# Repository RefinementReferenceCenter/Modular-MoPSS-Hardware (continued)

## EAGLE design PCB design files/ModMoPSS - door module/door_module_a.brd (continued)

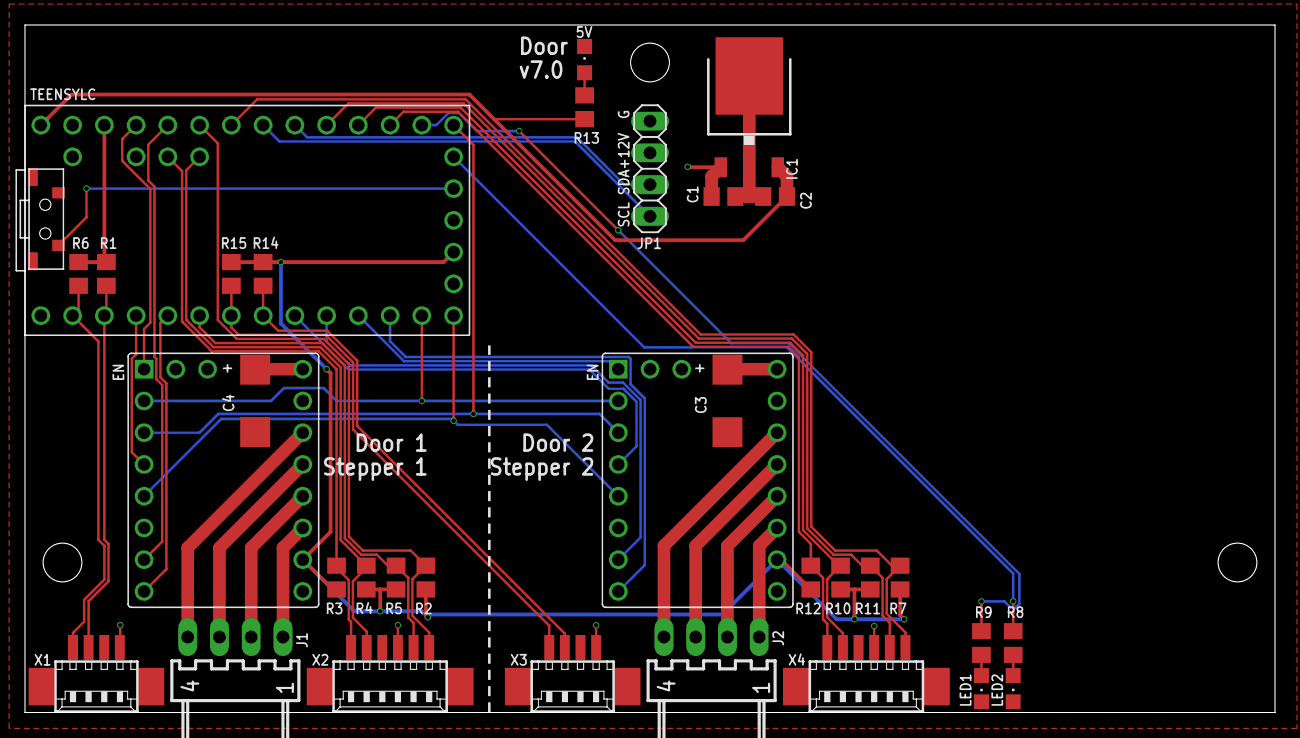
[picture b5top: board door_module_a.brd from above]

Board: 2 copper layers, 100.0 x 55.0 mm, 34 parts (0 on the bottom side), 43 nets.

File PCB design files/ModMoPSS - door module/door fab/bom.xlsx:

Comment | Designator | Footprint | JLCPCB Part #（optional）
red | 5V | CHIPLED_0805 | C84256
u33 | C1 | C0805 | C1740
u1 | C2 | C0805 | C49678
100u16v | C3 | SMC_C | C11375
100u16v | C4 | SMC_C | C11375
7805_TO252 | IC1 | TO252 | C233417
red | LED1 | CHIPLED_0805 | C84256
red | LED2 | CHIPLED_0805 | C84256
47k | R1 | R0805 | C17713
47k | R2 | R0805 | C17713
47k | R3 | R0805 | C17713
47k | R4 | R0805 | C17713
47k | R5 | R0805 | C17713
47k | R6 | R0805 | C17713
47k | R7 | R0805 | C17713
15k | R8 | R0805 | C17475
15k | R9 | R0805 | C17475
47k | R10 | R0805 | C17713
47k | R11 | R0805 | C17713
47k | R12 | R0805 | C17713
20k | R13 | R0805 | C4328
47k | R14 | R0805 | C17713
47k | R15 | R0805 | C17713
KH-3635-CAJ | S1 | KH-3635-CAJ | C530670
53261-04 | X1 | 53261-04 | C127368
53261-06 | X2 | 53261-06 | C99277
53261-04 | X3 | 53261-04 | C127368
53261-06 | X4 | 53261-06 | C99277

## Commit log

2023-02-14 Create ModMoPSS Gate parrts
2023-02-14 Create temp
2023-09-27 FAB NOT UPDATED - Fixed polarity labels on silk for Hive A
    Hive A: + and GND/S were switched on the silk layer, fixed. WARNING: I HAVE NOT UPDATED THE FAB FILESgit add PCB\ design\ files/ModMoPSS\ -\ Hive\ module\ A/hive_module.brd!
2023-11-22 Gate parts compatible with 40mm OD Acrylic tubes
2023-12-20 Added door for aux Power
2025-07-09 Fix for non functional level shifting
    Update to fix non functional level shifting on DMOD and CLK pins
2025-07-09 Fix for non functional level shifting
    Update to fix non functional level shifting on DMOD and CLK pins, GERBERS
